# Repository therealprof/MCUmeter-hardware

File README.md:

# The MCUmeter

The MCUmeter started as a gift for a "secret santa" round at my favourite electronics club, the [Boldport Club](https://www.boldport.com/). It was something I always wanted to do because it's useful, simple to build and can offers a nice learning experience for people who want to do microcontroller based hardware themselves.

## What is it?

In a nutshell it’s a high performance voltage/current/power monitor which will render it’s voltags/current/power readings supplied by a Texas Instruments INA260 via a STM32F042 microcontroller onto a small OLED display.

It consists of two main ingredients:

-   Custom made hardware, which is what this repository is all about
-   Software which is written in Rust and can be found [here](https://github.com/therealprof/MCUmeter-software) or directly on [crates.io](https://crates.io/crates/mcumeter)

The hardware design was done in KiCad and this repository contains both the KiCad 5 design files as well as the Gerber files which can be sent directly to a fab house to build the project, like the one I used for the prototypes. If you'd like you can order them directly from Aisler using [this link](https://aisler.net/p/ARZKLTZG).

This is what the boards look like:  and 

## Hardware connections

The [INA260](http://www.ti.com/lit/ds/symlink/ina260.pdf) allows sensing voltages (DC and positive values only!) up to 36V and high-side as well as low-side currenty (polarity not relevant). It can also do the power calculations, although at reduced precision.

The connections (from left to right) are

-   V_IN:  Positive voltage to be measured. Important! This power meter does not like negative voltages so watch the polarity!
-   I\_IN+/I\_IN-: High-side (i.e. connected between the power supply and DUT) or Low-side (i.e. connected between ground and the DUT) current measuring. Polarity irrelevant.
-   GND: Ground of voltage measurement, common with the rest of the circuit

It also provides a 4-pin header to connect a SSD1306 OLED display with I2C interface using the following pinout:

-   VCC
-   Ground
-   SCL
-   SDA

The connectors can be either soldered onto the board or screwed on, good results have been achieved with e.g. MC/Stäubli XUB-G

## Can I reuse the hardware for my own ideas?

Absolutely, everything is licensed under the BSD license so please go ahead and use it however you'd like.

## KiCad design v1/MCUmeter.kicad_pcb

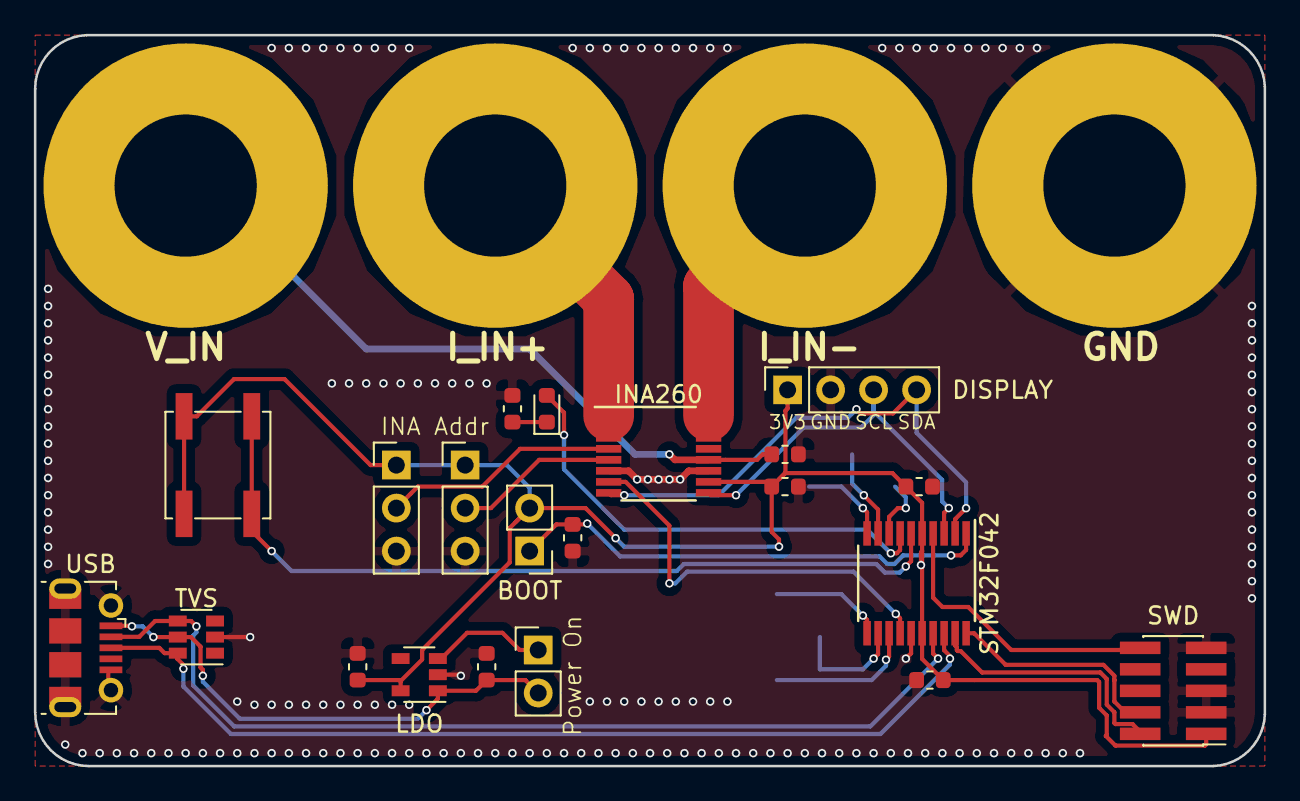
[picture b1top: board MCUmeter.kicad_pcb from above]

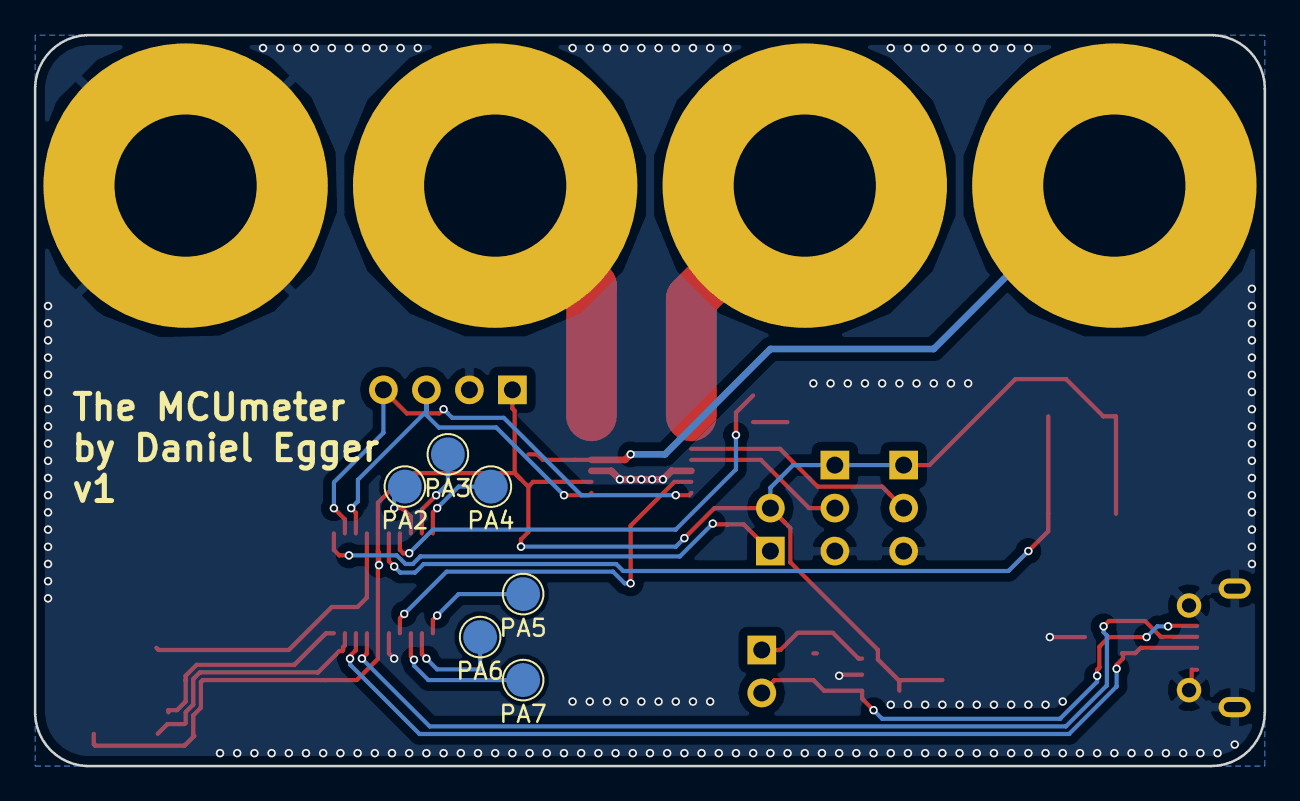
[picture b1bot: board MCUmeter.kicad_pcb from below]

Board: 2 copper layers, 72.6 x 43.2 mm, 31 parts (6 on the bottom side), 27 nets.

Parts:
BOOT: Conn_01x02; PinHeader_1x02_P2.54mm_Vertical
C1, C4: 1µ; C_0603_1608Metric
C2, C3, C5, C6: 100n; C_0603_1608Metric
D1: LED; LED_0603_1608Metric
DISPLAY: Conn_01x04_Female; PinSocket_1x04_P2.54mm_Vertical
H1, H2, H3, H4: MountingHole_Pad; MountingHole_8.4mm_M8_Pad
INA260: INA260; TSSOP-16_4.4x5mm_P0.65mm
J5, J6: Conn_01x03; PinHeader_1x03_P2.54mm_Vertical
J9: Conn_01x02; PinHeader_1x02_P2.54mm_Vertical
LDO: MIC5504-3.3YM5; SOT-23-5
PA2, PA3, PA4, PA5, PA6, PA7: TestPoint; TestPoint_Pad_D2.0mm
R1: 10k; R_0603_1608Metric
R2: 500R; R_0603_1608Metric
STM32F042: STM32F042F6Px; TSSOP-20_4.4x6.5mm_P0.65mm
SW1: SW_Push; SW_SPST_EVPBF
SWD: Conn_ARM_JTAG_SWD_10; PinHeader_2x05_P1.27mm_Vertical_SMD
TVS: USBLC6-2SC6; SOT-23-6
USB: USB_B_Micro; USB_Micro-B_Molex-105017-0001

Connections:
+3V3: BOOT.2, C2.1, C3.2, C4.1, C6.1, DISPLAY.1, INA260.10, J5.1, J6.1, LDO.5, STM32F042.5, STM32F042.16, SW1.2, SWD.1
/ALERT: INA260.7, STM32F042.14
/HIGH: C5.1, H1.1, INA260.12
/IN+: H2.1, INA260.1, INA260.2, INA260.3
/IN-: H3.1, INA260.14, INA260.15, INA260.16
/SCL: DISPLAY.3, INA260.9, STM32F042.3
/SDA: DISPLAY.4, INA260.8, STM32F042.2
/SWDCLK: STM32F042.20, SWD.4
/SWDIO: STM32F042.19, SWD.2
/USB_DM: STM32F042.17, TVS.4, USB.2
/USB_DP: STM32F042.18, TVS.6, USB.3
/VBUS: C1.1, J9.2, LDO.1, TVS.5, USB.1
/~RST: STM32F042.4, SWD.10
GND: C1.2, C2.2, C3.1, C4.2, C5.2, C6.2, DISPLAY.2, H4.1, INA260.6, INA260.11, J5.3, J6.3, LDO.2, R1.2, R2.1, STM32F042.15, SWD.3, SWD.5, SWD.9, TVS.2, USB.5, USB.6
unnamed: D1.1, R2.2
unnamed: D1.2, STM32F042.7
unnamed: BOOT.1, R1.1, STM32F042.1
unnamed: INA260.4, J5.2
unnamed: INA260.5, J6.2
unnamed: J9.1, LDO.3
unnamed: STM32F042.6, SW1.1
unnamed: PA2.1, STM32F042.8
unnamed: PA3.1, STM32F042.9
unnamed: PA4.1, STM32F042.10
unnamed: PA5.1, STM32F042.11
unnamed: PA6.1, STM32F042.12
unnamed: PA7.1, STM32F042.13

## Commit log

2018-12-26 First version of the MCUmeter hardware
2018-12-27 Added BSD license
2018-12-27 Added a bit more details in a README.md
2019-01-06 Added images and some more info about the hardware
